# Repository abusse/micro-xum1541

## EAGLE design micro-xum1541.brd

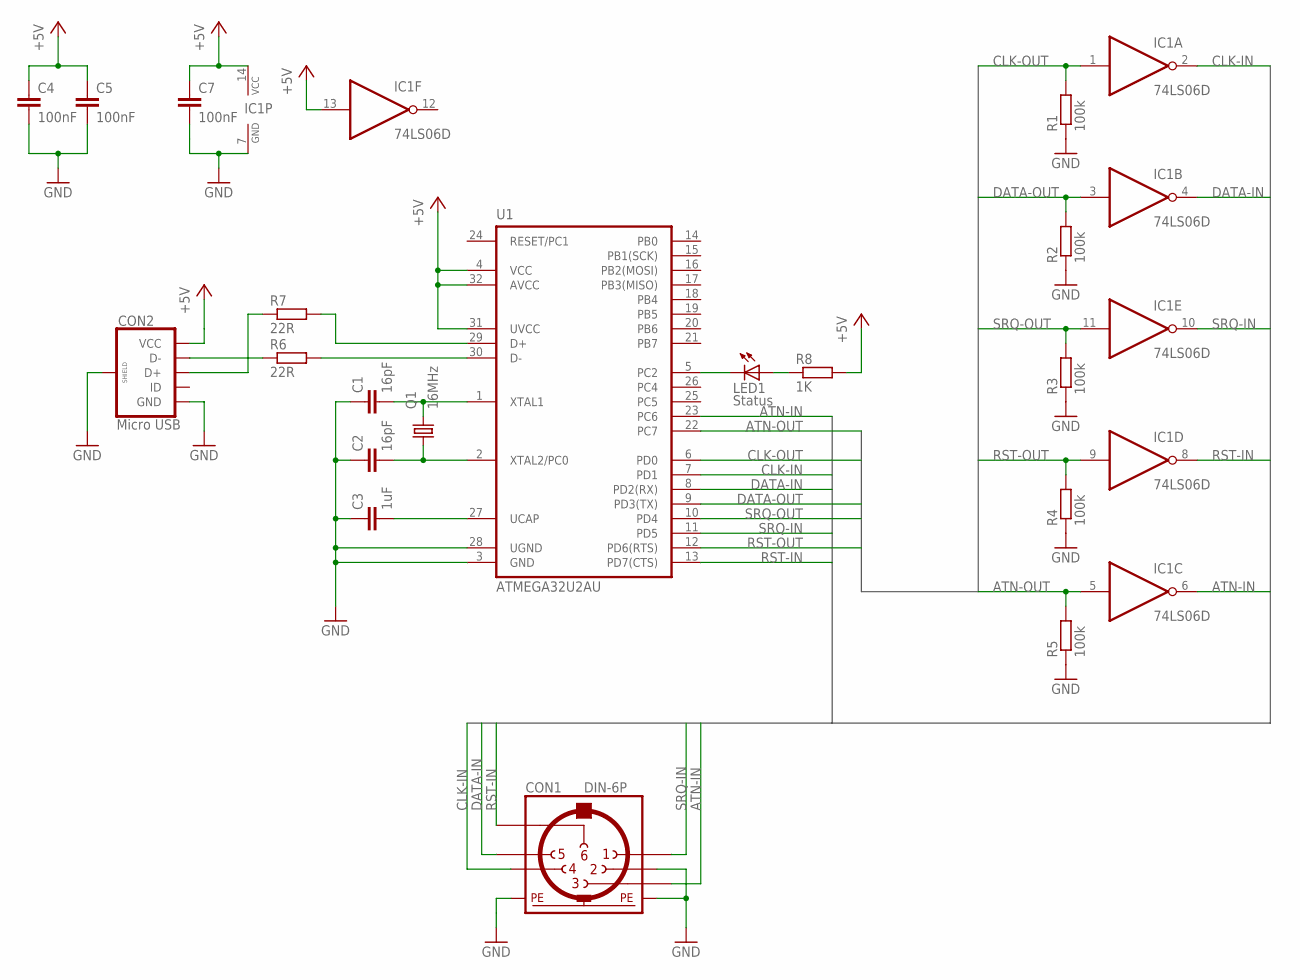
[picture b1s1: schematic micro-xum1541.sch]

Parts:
C1, C2: 16pF; C0603K
C3: 1uF; C0603
C4, C5: 100nF; C0603
C7: 100nF; C0603K
CON1: DIN-6P; 6P
CON2: Micro USB; MICRO-USB
IC1: 74LS06D; SO14
LED1: Status; CHIP-LED0805
Q1: 16MHz; 2.5X2.0_KX-6
R1, R2, R3, R4, R5: 100k; R0603
R6, R7: 22R; R0603
R8: 1K; R0603
U1: ATMEGA32U2AU; TQFP32

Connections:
+5V: C4.1, C5.1, C7.1, CON2.VBUS (VCC), IC1.13 (I), IC1.14 (VCC), R8.2, U1.4 (VCC), U1.31 (UVCC), U1.32 (AVCC)
ATN-IN: CON1.3, IC1.6 (O), U1.23 (PC6)
ATN-OUT: IC1.5 (I), R5.2, U1.22 (PC7)
CLK-IN: CON1.4, IC1.2 (O), U1.7 (PD1)
CLK-OUT: IC1.1 (I), R1.2, U1.6 (PD0)
DATA-IN: CON1.5, IC1.4 (O), U1.8 (PD2(RX))
DATA-OUT: IC1.3 (I), R2.2, U1.9 (PD3(TX))
GND: C1.1, C2.1, C3.1, C4.2, C5.2, C7.2, CON1.2, CON1.PE1, CON1.PE2, CON2.GND, CON2.SH1 (SHIELD), CON2.SH2 (SHIELD), CON2.SH3 (SHIELD), CON2.SH4 (SHIELD), IC1.7 (GND), R1.1, R2.1, R3.1, R4.1, R5.1, U1.3 (GND), U1.28 (UGND)
unnamed: C3.2, U1.27 (UCAP)
unnamed: CON2.D-1 (D-), R6.1
unnamed: R6.2, U1.30 (D-)
unnamed: R7.2, U1.29 (D+)
unnamed: CON2.D+1 (D+), R7.1
unnamed: LED1.A, R8.1
unnamed: LED1.C, U1.5 (PC2)
RST-IN: CON1.6, IC1.8 (O), U1.13 (PD7(CTS))
RST-OUT: IC1.9 (I), R4.2, U1.12 (PD6(RTS))
SRQ-IN: CON1.1, IC1.10 (O), U1.11 (PD5)
SRQ-OUT: IC1.11 (I), R3.2, U1.10 (PD4)
XTAL1: C1.2, Q1.3 (2), U1.1 (XTAL1)
XTAL2: C2.2, Q1.1, U1.2 (XTAL2/PC0)

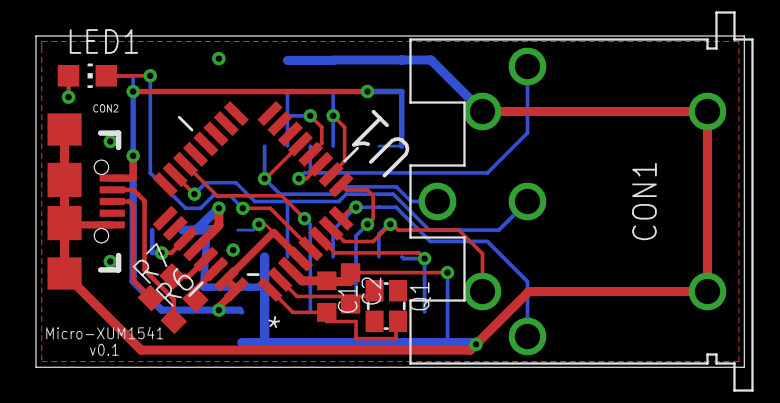
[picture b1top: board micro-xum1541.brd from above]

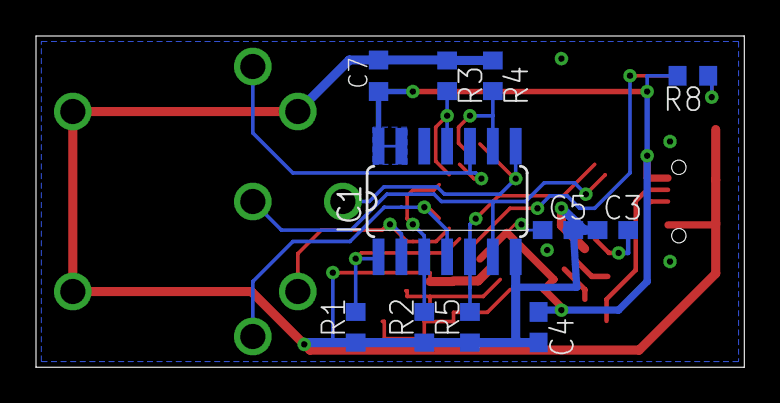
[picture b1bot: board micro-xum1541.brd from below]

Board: 2 copper layers, 39.4 x 18.4 mm, 20 parts (11 on the bottom side), 21 nets.

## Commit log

2018-07-19 Initial schematic commit

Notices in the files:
parts and their libraries:
crystal-geyer_V1_0: Copyright: Geyer-Electronic
